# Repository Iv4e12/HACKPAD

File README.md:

# Custom Gravity Falls Hackpad

A custom Gravity Falls-themed hackpad designed to encode and decode ciphers from the series.

## Features
* **Encode and decode** Gravity Falls ciphers
* **OLED display**
* **Rotary encoder** for menu navigation
* **Four switches** for mechanical input
* **Software** designed with Python
* **Custom-designed PCB**

## How I Built It
The hackpad uses a Seeed XIAO RP2040, an OLED screen, a rotary encoder, and four switches.

I designed the PCB myself using KiCad and wrote the software in Python. One of the biggest challenges was learning KiCad and finding the correct footprints for each component.

## Status of Project
* **Ready to order components**

## Media

## Credits
Designed and built by me, with light assistance from AI.

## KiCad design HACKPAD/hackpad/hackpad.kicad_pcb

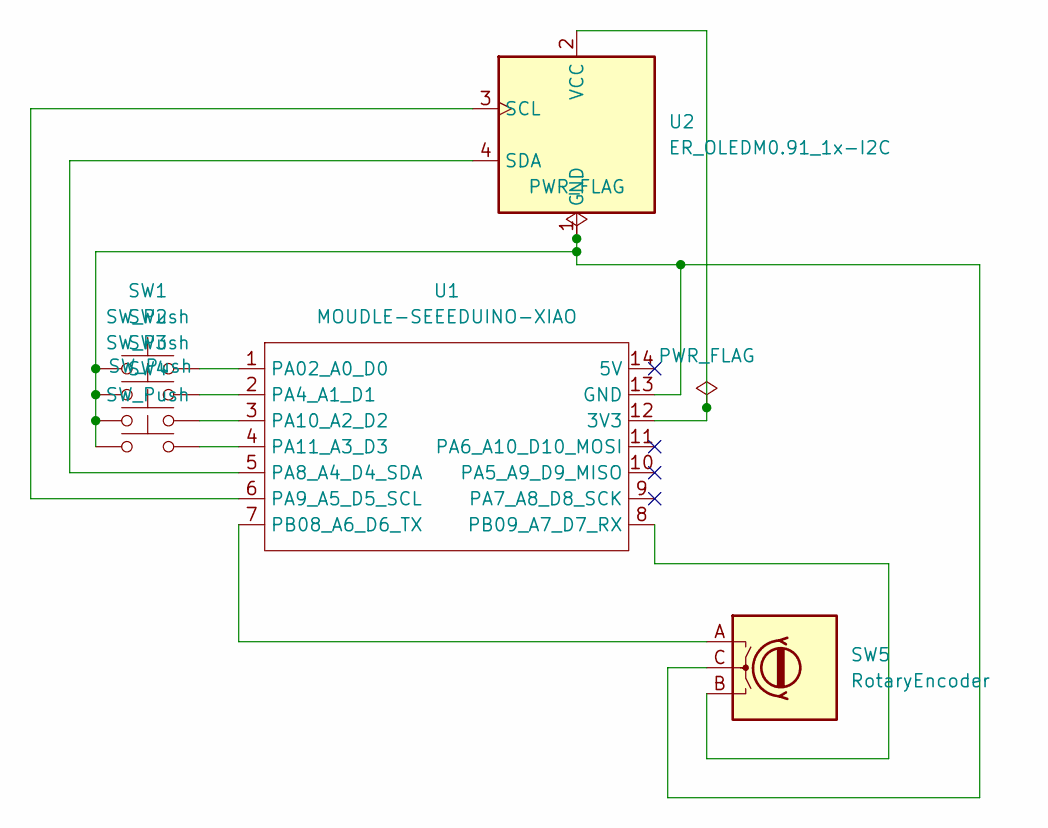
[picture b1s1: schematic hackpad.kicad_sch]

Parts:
SW1, SW2, SW3, SW4: SW_Push
SW5: RotaryEncoder
U1: MOUDLE-SEEEDUINO-XIAO
U2: ER_OLEDM0.91_1x-I2C

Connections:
unnamed: U1.12 (3V3), U2.2 (VCC)
unnamed: SW1.1, SW2.1, SW3.1, SW4.1, SW5.C, SW5.S2, U1.13 (GND), U2.1 (GND)
unnamed: SW1.2, U1.1 (PA02_A0_D0)
unnamed: SW2.2, U1.2 (PA4_A1_D1)
unnamed: SW5.S1, U1.9 (PA7_A8_D8_SCK)
unnamed: U1.5 (PA8_A4_D4_SDA), U2.4 (SDA)
unnamed: U1.6 (PA9_A5_D5_SCL), U2.3 (SCL)
unnamed: SW3.2, U1.3 (PA10_A2_D2)
unnamed: SW4.2, U1.4 (PA11_A3_D3)
unnamed: SW5.A, U1.7 (PB08_A6_D6_TX)
unnamed: SW5.B, U1.8 (PB09_A7_D7_RX)

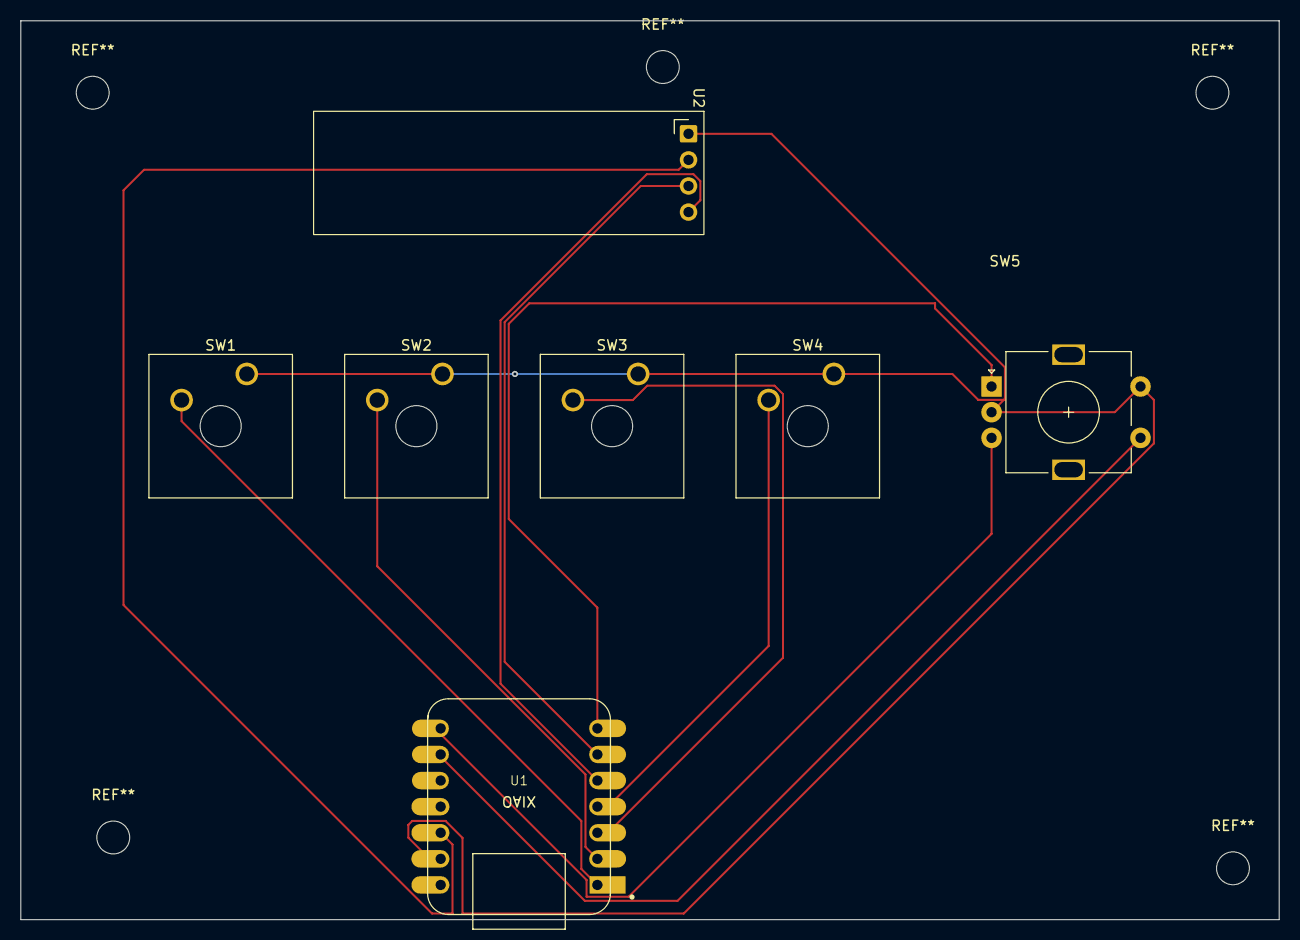
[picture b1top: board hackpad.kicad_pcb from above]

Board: 2 copper layers, 122.5 x 87.5 mm, 7 parts (0 on the bottom side), 11 nets.
